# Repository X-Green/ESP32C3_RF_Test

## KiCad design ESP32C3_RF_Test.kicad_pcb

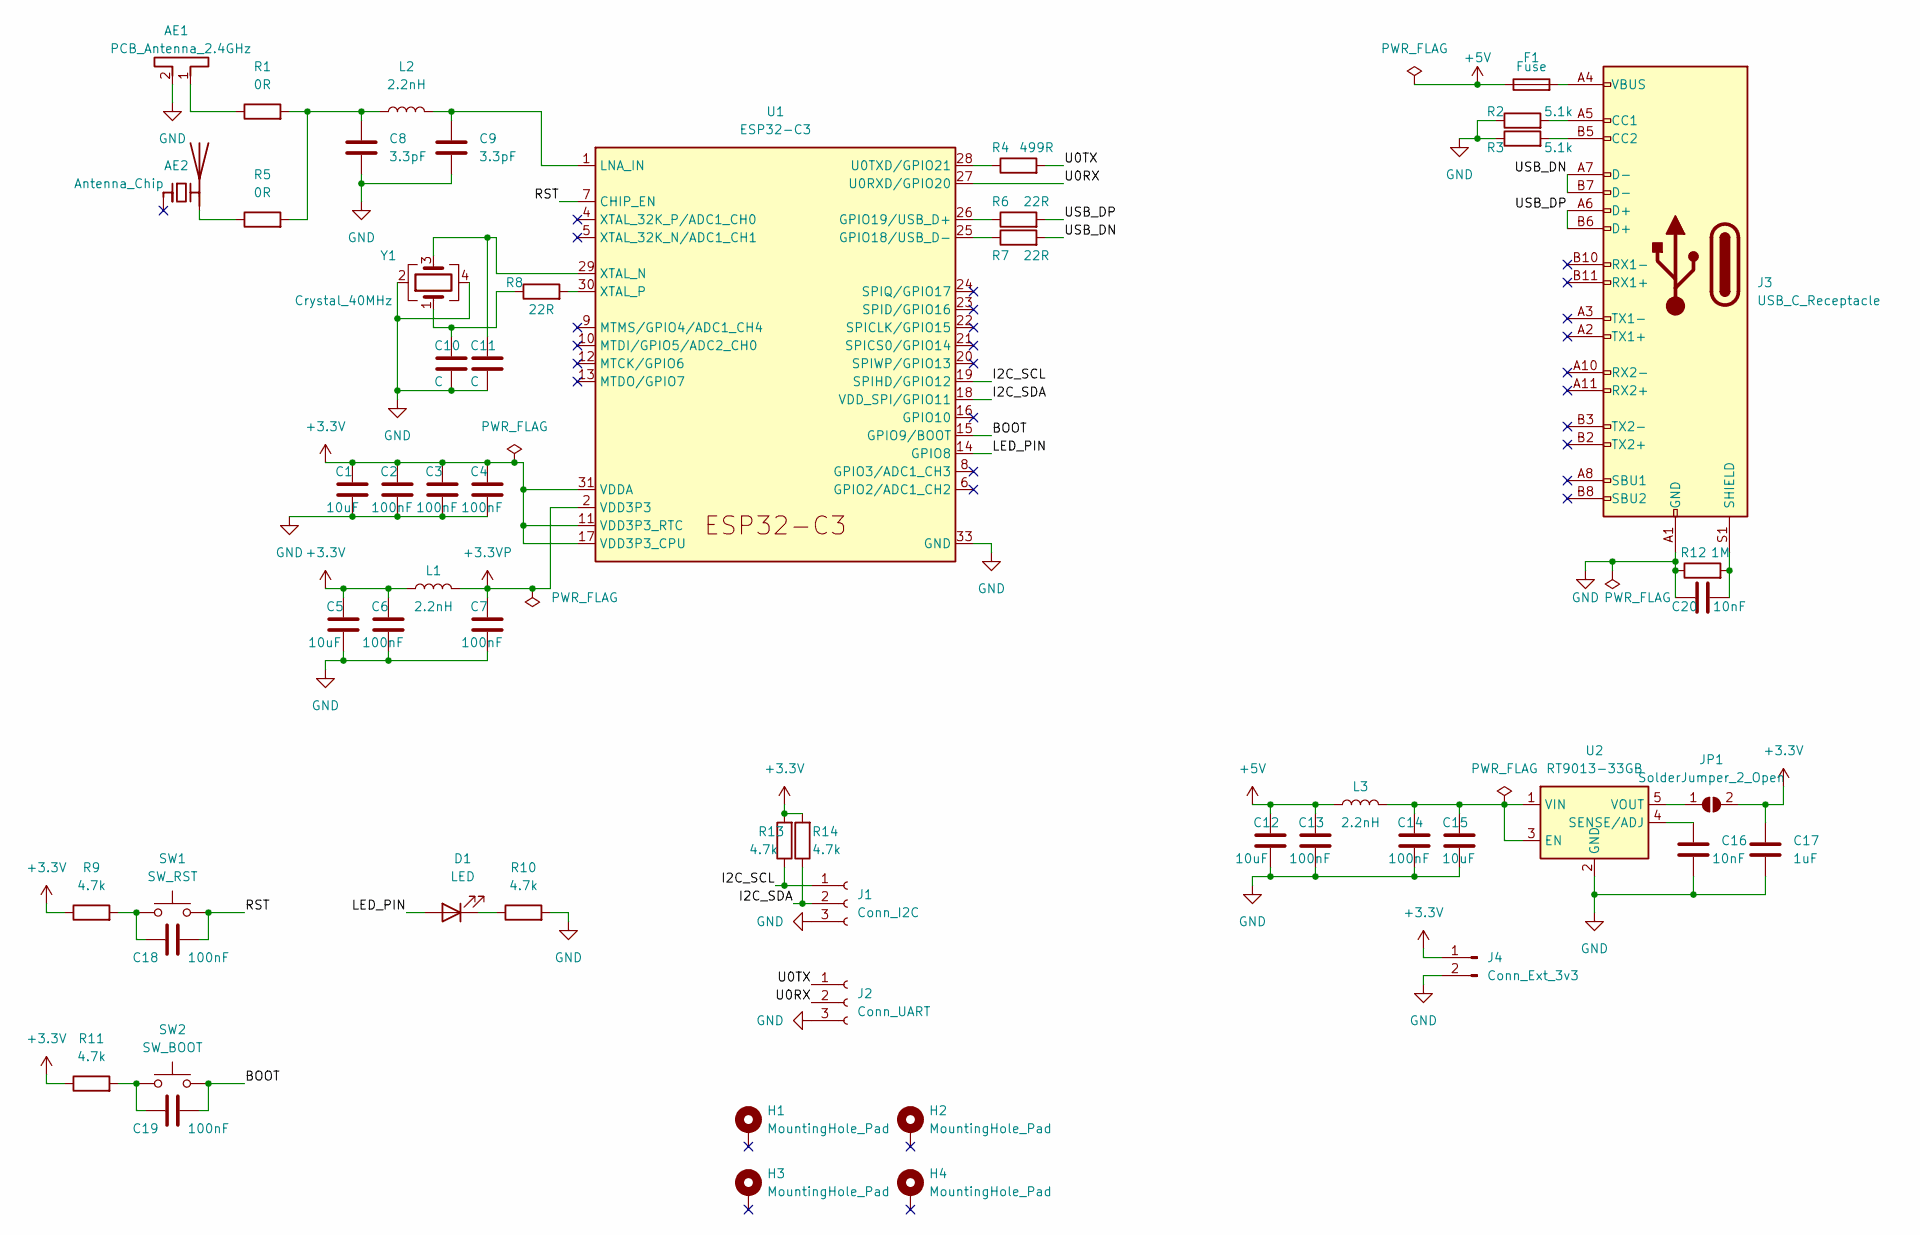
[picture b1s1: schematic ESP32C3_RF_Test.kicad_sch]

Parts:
AE1: PCB_Antenna_2.4GHz; Texas_SWRA117D_2.4GHz_Right
AE2: Antenna_Chip; Johanson_2450AT43F0100
C1, C5, C12, C15: 10uF; C_1206_3216Metric
C2, C3, C4, C6, C7, C13, C14, C18, C19: 100nF; C_0603_1608Metric
C8, C9: 3.3pF; C_0603_1608Metric
C10, C11: C; C_0603_1608Metric
C16, C20: 10nF; C_0603_1608Metric
C17: 1uF; C_0603_1608Metric
D1: LED; LED_0603_1608Metric
F1: Fuse; Fuse_1210_3225Metric
H1, H2, H3, H4: MountingHole_Pad; MountingHole_3.2mm_M3_Pad_Via
J1: Conn_I2C; PinHeader_1x03_P2.54mm_Vertical
J2: Conn_UART; PinHeader_1x03_P2.54mm_Vertical
J3: USB_C_Receptacle; USB_C_Receptacle_HRO_TYPE-C-31-M-12
J4: Conn_Ext_3v3; PinSocket_1x02_P2.54mm_Vertical
JP1: SolderJumper_2_Open; SolderJumper-2_P1.3mm_Open_TrianglePad1.0x1.5mm
L1, L2, L3: 2.2nH; L_0603_1608Metric
R1, R5: 0R; R_0603_1608Metric
R2, R3: 5.1k; R_0603_1608Metric
R4: 499R; R_0603_1608Metric
R6, R7, R8: 22R; R_0603_1608Metric
R9, R10, R11, R13, R14: 4.7k; R_0603_1608Metric
R12: 1M; R_0603_1608Metric
SW1: SW_RST; SW_Push_1P1T_NO_CK_KSC7xxJ
SW2: SW_BOOT; SW_Push_1P1T_NO_CK_KSC7xxJ
U1: ESP32-C3; QFN-32-1EP_5x5mm_P0.5mm_EP3.1x3.1mm_ThermalVias
U2: RT9013-33GB; TSOT-23-5
Y1: Crystal_40MHz; Crystal_SMD_3225-4Pin_3.2x2.5mm

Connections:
+3.3V: C1.1, C2.1, C3.1, C4.1, C5.1, C6.1, C17.1, J4.1, JP1.2 (B), L1.1, R9.1, R11.1, R13.2, R14.2, U1.11 (VDD3P3_RTC), U1.17 (VDD3P3_CPU), U1.31 (VDDA), U1.32 (VDDA)
+3.3VP: C7.1, L1.2, U1.2 (VDD3P3), U1.3 (VDD3P3)
+5V: C12.1, C13.1, F1.1, L3.1
/BOOT: C19.2, SW2.2, U1.15 (GPIO9/BOOT)
/I2C_SCL: J1.1, R13.1, U1.19 (SPIHD/GPIO12)
/I2C_SDA: J1.2, R14.1, U1.18 (VDD_SPI/GPIO11)
/LED_PIN: D1.2 (A), U1.14 (GPIO8)
/RST: C18.2, SW1.2, U1.7 (CHIP_EN)
/U0RX: J2.2, U1.27 (U0RXD/GPIO20)
/U0TX: J2.1, R4.2
/USB_DN: J3.A7 (D-), J3.B7 (D-), R7.2
/USB_DP: J3.A6 (D+), J3.B6 (D+), R6.2
GND: AE1.2, C1.2, C2.2, C3.2, C4.2, C5.2, C6.2, C7.2, C8.2, C9.2, C10.2, C11.2, C12.2, C13.2, C14.2, C15.2, C16.2, C17.2, C20.1, J1.3, J2.3, J3.A1 (GND), J3.A12 (GND), J3.B1 (GND), J3.B12 (GND), J4.2, R2.1, R3.1, R10.2, R12.1, U1.33 (GND), U2.2 (GND), Y1.2, Y1.4
unnamed: AE1.1, R1.1
unnamed: AE2.2 (PCB_Trace), R5.1
unnamed: C8.1, L2.1, R1.2, R5.2
unnamed: C9.1, L2.2, U1.1 (LNA_IN)
unnamed: C10.1, R8.1, Y1.1
unnamed: C11.1, U1.29 (XTAL_N), Y1.3
unnamed: C14.1, C15.1, L3.2, U2.1 (VIN), U2.3 (EN)
unnamed: C16.1, U2.4 (SENSE/ADJ)
unnamed: C18.1, R9.2, SW1.1
unnamed: C19.1, R11.2, SW2.1
unnamed: C20.2, J3.S1 (SHIELD), R12.2
unnamed: D1.1 (K), R10.1
unnamed: F1.2, J3.A4 (VBUS), J3.A9 (VBUS), J3.B4 (VBUS), J3.B9 (VBUS)
unnamed: J3.A5 (CC1), R2.2
unnamed: J3.B5 (CC2), R3.2
unnamed: JP1.1 (A), U2.5 (VOUT)
unnamed: R4.1, U1.28 (U0TXD/GPIO21)
unnamed: R6.1, U1.26 (GPIO19/USB_D+)
unnamed: R7.1, U1.25 (GPIO18/USB_D-)
unnamed: R8.2, U1.30 (XTAL_P)

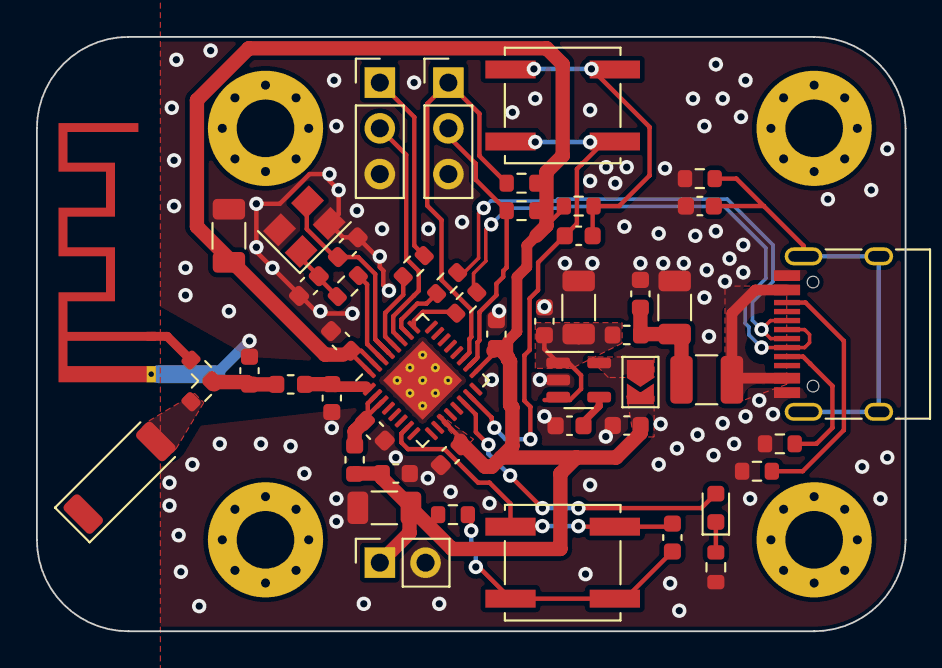
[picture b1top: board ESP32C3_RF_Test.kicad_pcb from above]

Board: 2 copper layers, 48.3 x 33.0 mm, 55 parts (0 on the bottom side), 33 nets.

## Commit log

2023-02-16 init
2023-02-16 ignore
2023-02-16 remove 3d
2023-02-16 BOM change
